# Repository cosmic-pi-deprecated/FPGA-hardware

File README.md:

# FPGA-hardware
FPGA main board for Cosmic Pi

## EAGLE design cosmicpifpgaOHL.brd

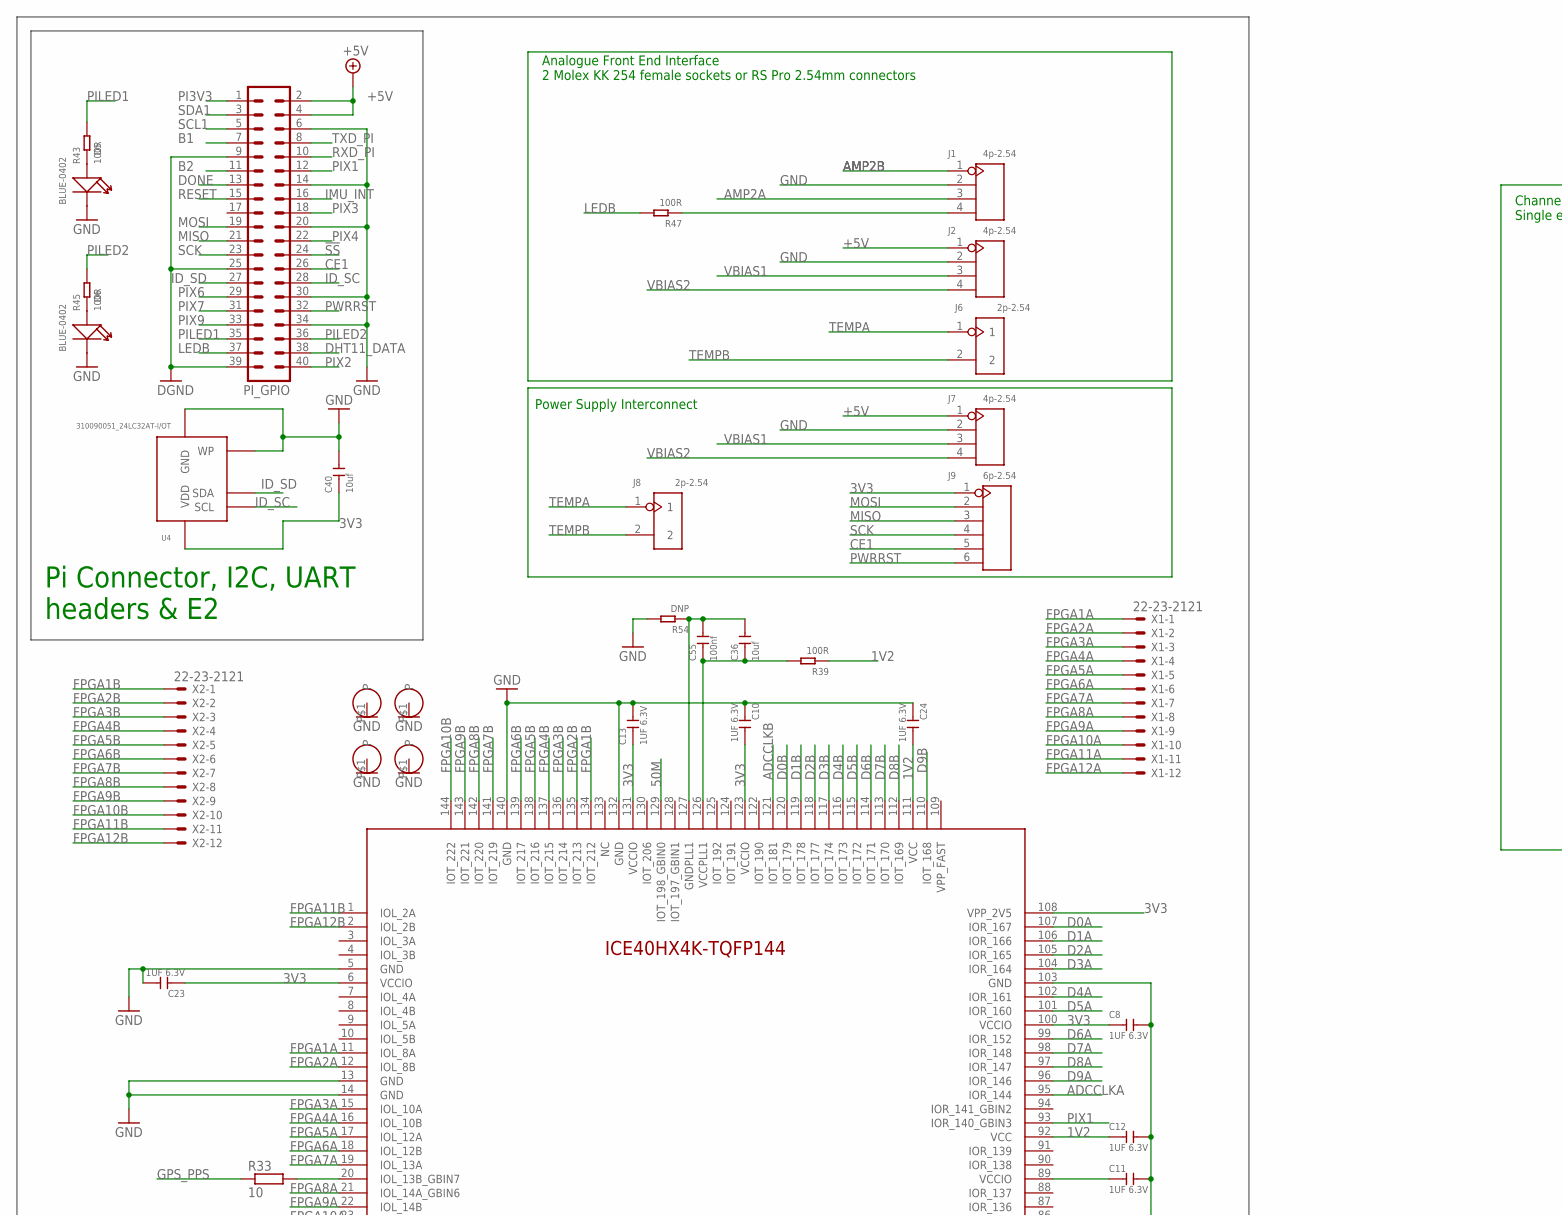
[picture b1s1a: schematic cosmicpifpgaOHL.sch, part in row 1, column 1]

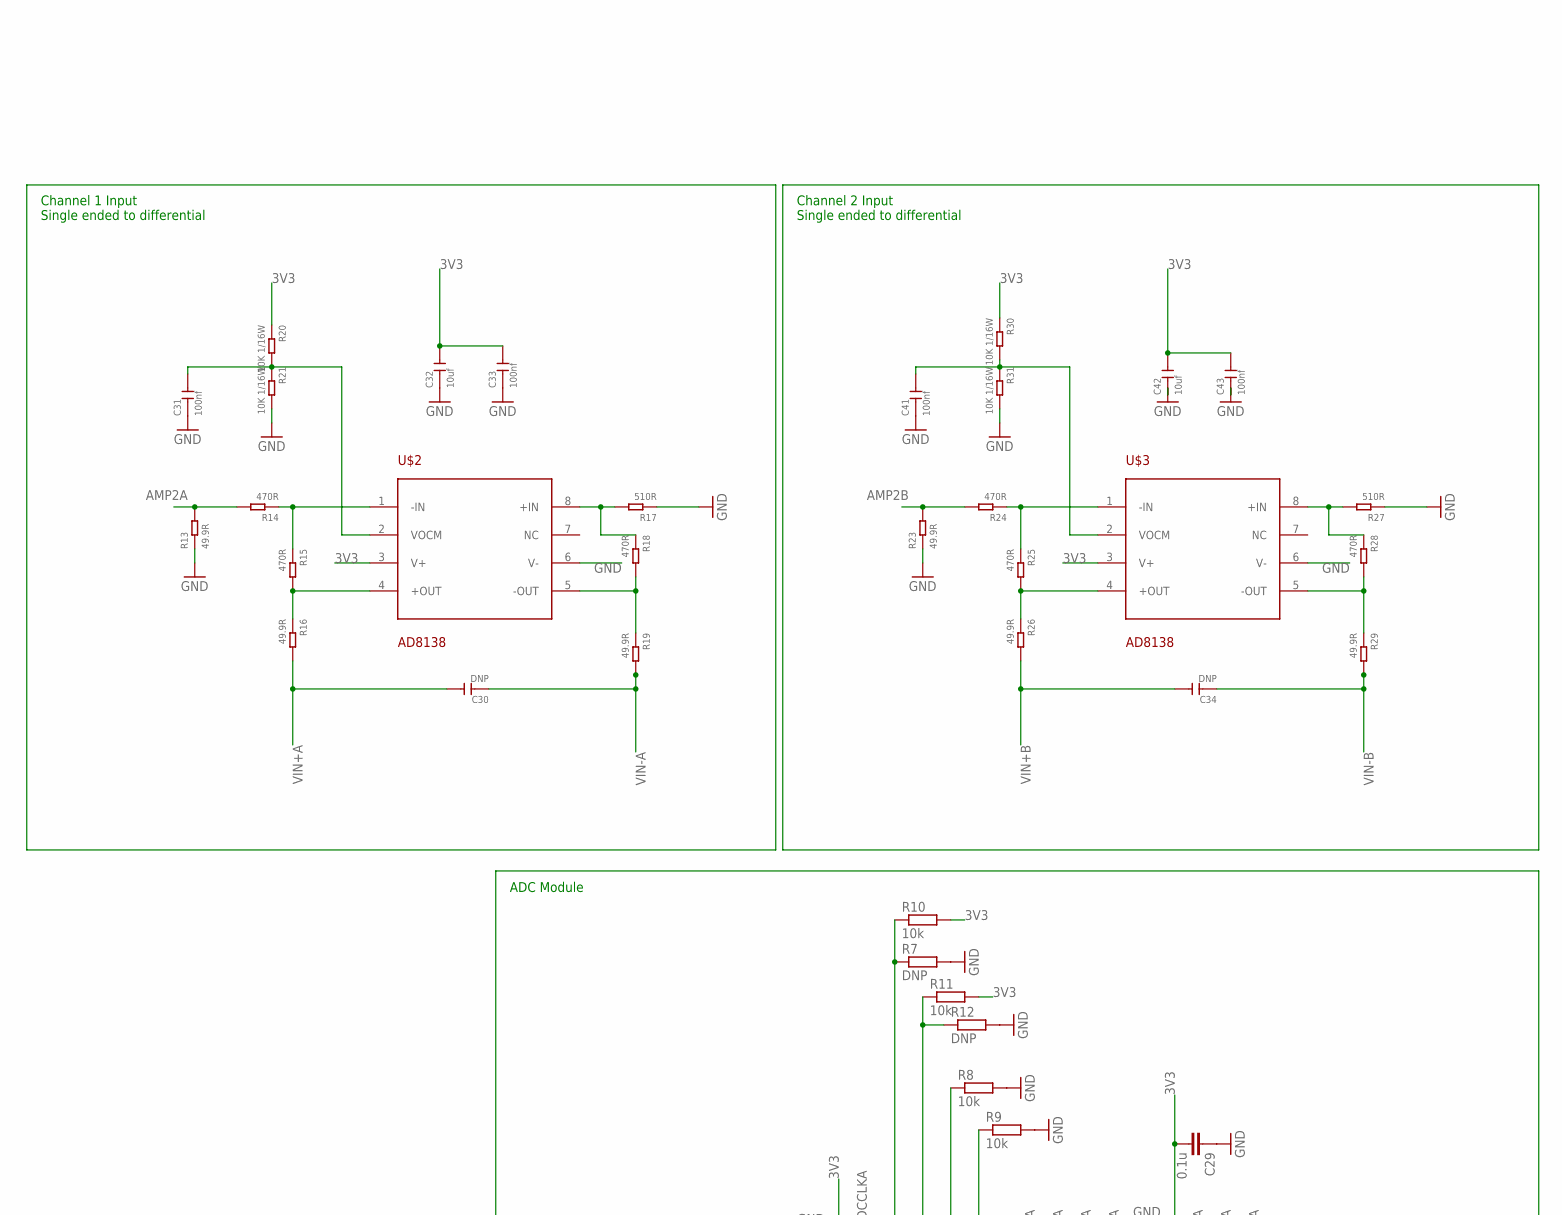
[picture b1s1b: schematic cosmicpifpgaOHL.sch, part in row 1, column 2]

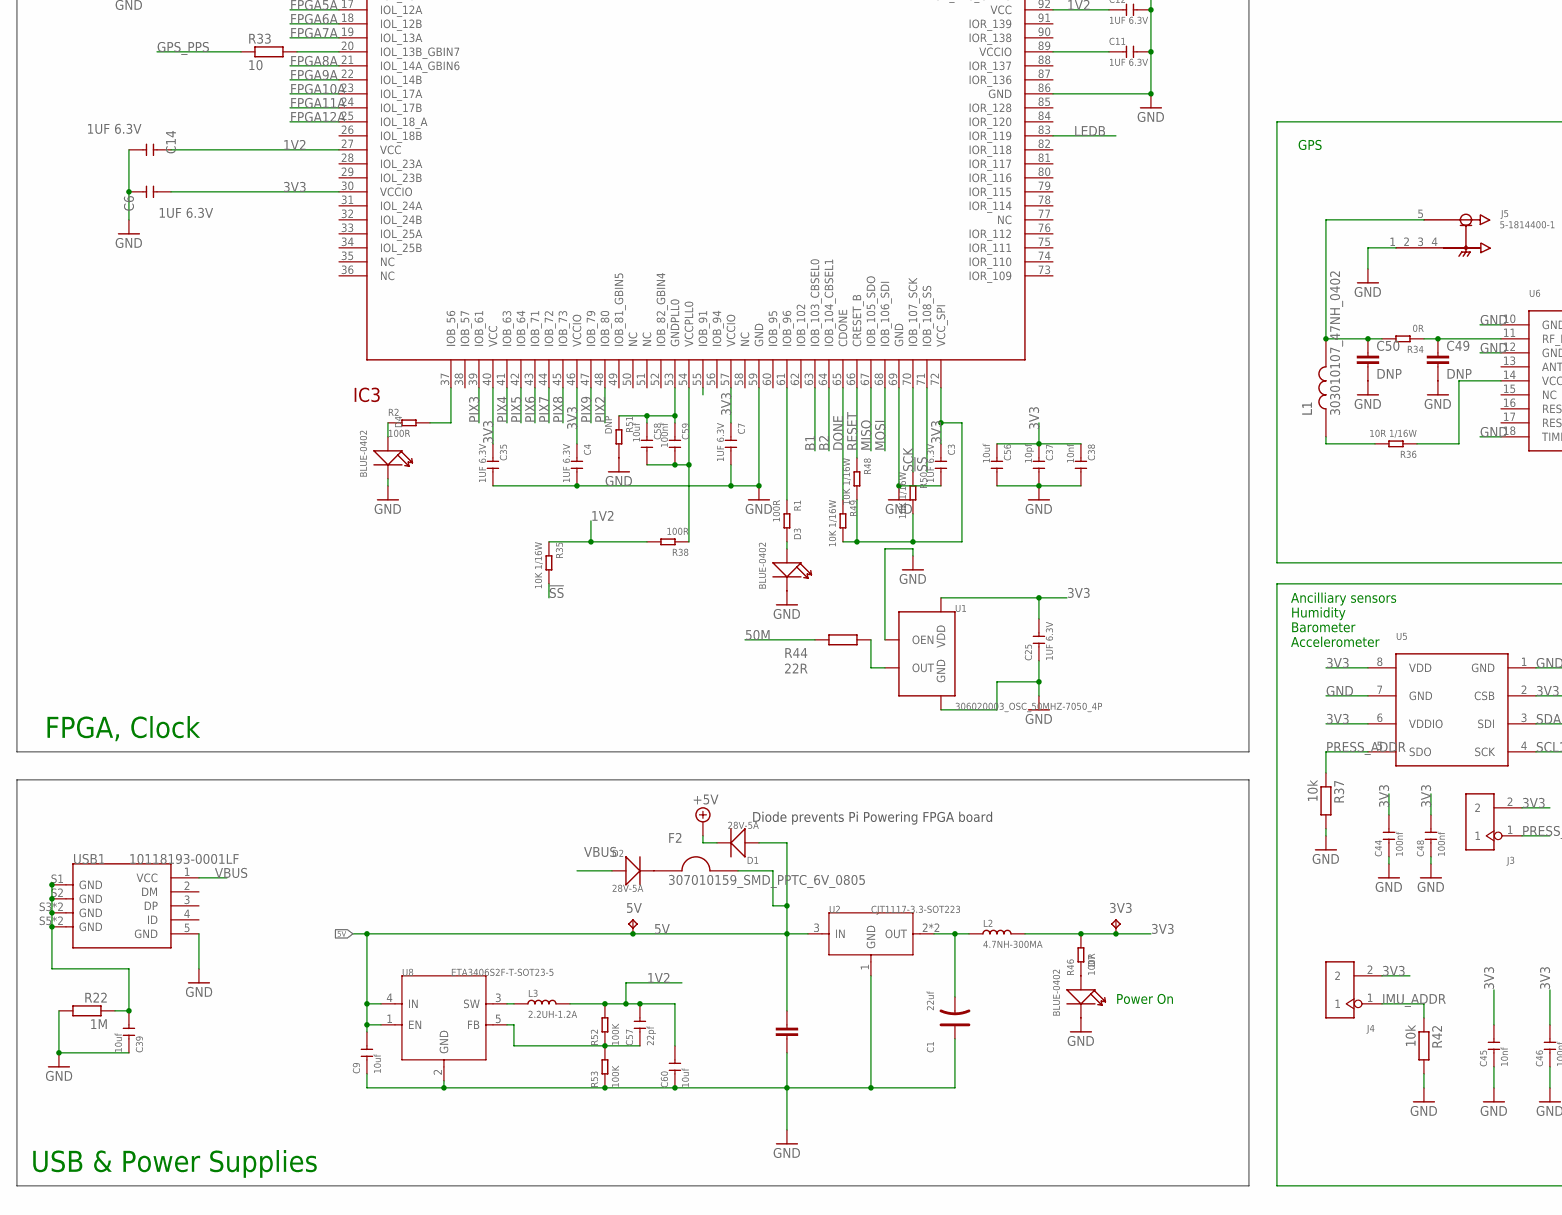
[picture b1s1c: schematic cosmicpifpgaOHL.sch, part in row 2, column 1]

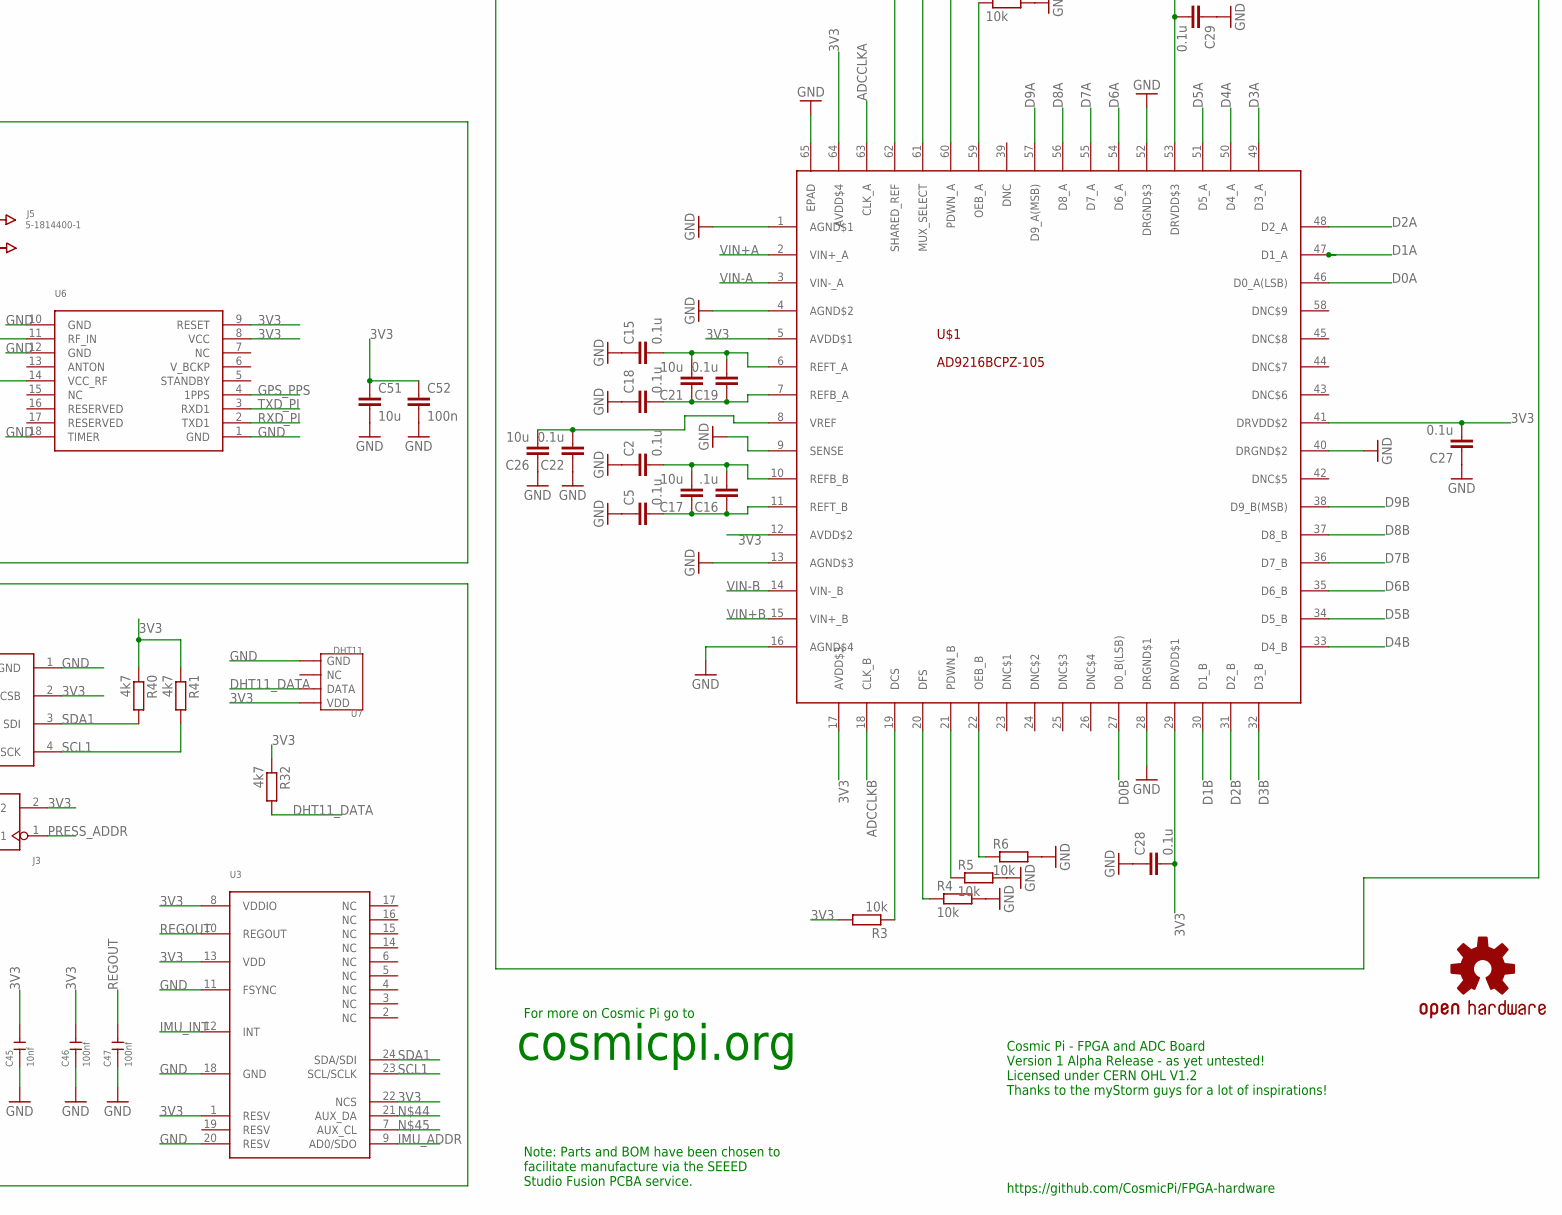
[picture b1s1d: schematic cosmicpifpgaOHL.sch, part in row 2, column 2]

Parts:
3V3, 5V: TPB1,27; B1,27
C1: 22uf; AVX-B
C2, C5, C15, C18, C19, C22, C27, C28, C29: 0.1u; C0402
C3, C4, C6, C7, C8, C10, C11, C12, C13, C14, C23, C24, C25, C35: 1UF 6.3V; C0402
C9, C32, C36, C39, C40, C42, C56, C58, C60: 10uf; C0402
C16: .1u; C0402
C17, C21, C26, C51: 10u; C0402
C20: 47uF; 1206
C30, C34: DNP; C0603
C31, C33, C41, C43, C44, C46, C47, C48, C55, C59: 100nf; C0402
C37: 10pf; C0402
C38, C45: 10nf; C0402
C49, C50: DNP; C0402
C52: 100n; C0402
C57: 22pf; C0402
D1, D2: 28V-5A; DO-214AA
D3, D4, D5, D6, D7: BLUE-0402; LED-0402
F2: 307010159_SMD_PPTC_6V_0805; F0805
IC3: ICE40HX4K_TQFP144; TQFP144
J1, J2, J7: 4p-2.54; H4-2.54
J3, J4: DIP-BLACK-JUMPER; H2-2.54
J5: 5-1814400-1; TE_5-1814400-1
J6, J8: 2p-2.54; H2-2.54
J9: 6p-2.54; H6-2.54
L1: 303010107_47NH_0402; L0402
L2: 4.7NH-300MA; L0402
L3: 2.2UH-1.2A; L0805
OSHW: OSHW-LOGOL; OSHW-LOGO-L
PI_GPIO: MA20-2
R1, R2, R38, R39, R43, R45, R46, R47: 100R; R0402
R3, R4, R5, R6, R8, R9, R10, R11, R37, R42: 10k; R0402
R7, R12, R51, R54: DNP; R0402
R13, R16, R19, R23, R26, R29: 49.9R; R0603
R14, R15, R18, R24, R25, R28: 470R; R0603
R17, R27: 510R; R0603
R20, R21, R30, R31, R35, R48, R49, R50: 10K 1/16W; R0402
R22: 1M; R0402
R32, R40, R41: 4k7; R0402
R33: 10; R0402
R34: 0R; R0402
R36: 10R 1/16W; R0402
R44: 22R; R0402
R52, R53: 100K; R0402
U1: 306020003_OSC_50MHZ-7050_4P; X7050_4P
U2: CJT1117-3.3-SOT223; SOT-223
U3: MPU-9250
U4: 310090051_24LC32AT-I/OT; SOT235
U5: BMP280
U6: L70-M39
U7: DHT11; SNR4-2.54-15.5X12.0X5.5MM
U8: ETA3406S2F-T-SOT23-5; SOT-23-5
U$1: AD9216BCPZ-105; QFN50P900X900X100-65N
U$2, U$3: AD8138; SOP65P490X110-8N
U$16, U$21, U$22, U$24: HOLE-2.5MM; 2.5MM-HOLE
USB1: 10118193-0001LF; MICRO-USB5+6P-SMD-0.65-B
X1, X2: 22-23-2121

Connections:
1V2: C12.1, C14.1, C24.2, C57.2, C60.2, IC3.27 (VCC), IC3.92 (VCC), IC3.111 (VCC), L3.2, R35.1, R38.2, R39.1, R52.2
3V3: 3V3.TP, C3.1, C4.1, C6.2, C7.1, C8.1, C10.2, C13.1, C23.1, C25.2, C27.2, C28.2, C29.2, C32.2, C33.2, C35.1, C37.1, C38.1, C40.1, C42.2, C43.2, C44.2, C45.2, C46.2, C48.2, C51.1, C52.1, C56.1, IC3.6 (VCCIO), IC3.30 (VCCIO), IC3.40 (VCC), IC3.46 (VCCIO), IC3.57 (VCCIO), IC3.72 (VCC_SPI), IC3.100 (VCCIO), IC3.108 (VPP_2V5), IC3.123 (VCCIO), IC3.131 (VCCIO), J3.2, J4.2, J9.1, L2.2, R3.2, R10.2, R11.2, R20.1, R30.1, R32.1, R40.1, R41.1, R46.2, R48.2, R49.2, R50.2, U1.P$4 (VDD), U3.1 (RESV), U3.8 (VDDIO), U3.13 (VDD), U3.22 (NCS), U4.4 (VDD), U5.2 (CSB), U5.6 (VDDIO), U5.8 (VDD), U6.8 (VCC), U6.9 (RESET), U7.1 (VDD), U$1.5 (AVDD$1), U$1.12 (AVDD$2), U$1.17 (AVDD$3), U$1.29 (DRVDD$1), U$1.41 (DRVDD$2), U$1.53 (DRVDD$3), U$1.64 (AVDD$4), U$2.3 (V+), U$3.3 (V+)
5V: 5V.TP, C9.2, C20.1, D1.+, F2.P$2, U2.3 (IN), U8.1 (EN), U8.4 (IN)
50M: IC3.129 (IOT_198_GBIN0), R44.2
!SS: IC3.71 (IOB_108_SS), PI_GPIO.24, R35.2
+5V: D1.-, J2.1, J7.1, PI_GPIO.2, PI_GPIO.4
ADCCLKA: IC3.95 (IOR_144), U$1.63 (CLK_A)
ADCCLKB: IC3.121 (IOT_181), U$1.18 (CLK_B)
AMP2A: J1.3, R13.2, R14.2
AMP2B: J1.1, R23.2, R24.2
B1: IC3.63 (IOB_103_CBSEL0), PI_GPIO.7
B2: IC3.64 (IOB_104_CBSEL1), PI_GPIO.11
CE1: J9.5, PI_GPIO.26
D0A: IC3.107 (IOR_167), U$1.46 (D0_A(LSB))
D0B: IC3.120 (IOT_179), U$1.27 (D0_B(LSB))
D1A: IC3.106 (IOR_166), U$1.47 (D1_A)
D1B: IC3.119 (IOT_178), U$1.30 (D1_B)
D2A: IC3.105 (IOR_165), U$1.48 (D2_A)
D2B: IC3.118 (IOT_177), U$1.31 (D2_B)
D3A: IC3.104 (IOR_164), U$1.49 (D3_A)
D3B: IC3.117 (IOT_174), U$1.32 (D3_B)
D4A: IC3.102 (IOR_161), U$1.50 (D4_A)
D4B: IC3.116 (IOT_173), U$1.33 (D4_B)
D5A: IC3.101 (IOR_160), U$1.51 (D5_A)
D5B: IC3.115 (IOT_172), U$1.34 (D5_B)
D6A: IC3.99 (IOR_152), U$1.54 (D6_A)
D6B: IC3.114 (IOT_171), U$1.35 (D6_B)
D7A: IC3.98 (IOR_148), U$1.55 (D7_A)
D7B: IC3.113 (IOT_170), U$1.36 (D7_B)
D8A: IC3.97 (IOR_147), U$1.56 (D8_A)
D8B: IC3.112 (IOT_169), U$1.37 (D8_B)
D9A: IC3.96 (IOR_146), U$1.57 (D9_A(MSB))
D9B: IC3.110 (IOT_168), U$1.38 (D9_B(MSB))
DHT11_DATA: PI_GPIO.38, R32.2, U7.2 (DATA)
DONE: IC3.65 (CDONE), PI_GPIO.13, R49.1
FPGA1A: IC3.11 (IOL_8A), X1.1
FPGA1B: IC3.134 (IOT_212), X2.1
FPGA2A: IC3.12 (IOL_8B), X1.2
FPGA2B: IC3.135 (IOT_213), X2.2
FPGA3A: IC3.15 (IOL_10A), X1.3
FPGA3B: IC3.136 (IOT_214), X2.3
FPGA4A: IC3.16 (IOL_10B), X1.4
FPGA4B: IC3.137 (IOT_215), X2.4
FPGA5A: IC3.17 (IOL_12A), X1.5
FPGA5B: IC3.138 (IOT_216), X2.5
FPGA6A: IC3.18 (IOL_12B), X1.6
FPGA6B: IC3.139 (IOT_217), X2.6
FPGA7A: IC3.19 (IOL_13A), X1.7
FPGA7B: IC3.141 (IOT_219), X2.7
FPGA8A: IC3.21 (IOL_14A_GBIN6), X1.8
FPGA8B: IC3.142 (IOT_220), X2.8
FPGA9A: IC3.22 (IOL_14B), X1.9
FPGA9B: IC3.143 (IOT_221), X2.9
FPGA10A: IC3.23 (IOL_17A), X1.10
FPGA10B: IC3.144 (IOT_222), X2.10
FPGA11A: IC3.24 (IOL_17B), X1.11
FPGA11B: IC3.1 (IOL_2A), X2.11
FPGA12A: IC3.25 (IOL_18_A), X1.12
FPGA12B: IC3.2 (IOL_2B), X2.12
GND: C1.+, C2.1, C3.2, C4.2, C5.1, C6.1, C7.2, C8.2, C9.1, C10.1, C11.2, C12.2, C13.2, C14.2, C15.1, C18.1, C20.2, C22.1, C23.2, C24.1, C25.1, C26.1, C27.1, C28.1, C29.1, C31.1, C32.1, C33.1, C35.2, C37.2, C38.2, C39.1, C40.2, C41.1, C42.1, C43.1, C44.1, C45.1, C46.1, C47.1, C48.1, C49.2, C50.2, C51.2, C52.2, C56.2, C60.1, D3.-, D4.-, D5.-, D6.-, D7.-, IC3.5 (GND), IC3.13 (GND), IC3.14 (GND), IC3.59 (GND), IC3.69 (GND), IC3.86 (GND), IC3.103 (GND), IC3.132 (GND), IC3.140 (GND), J1.2, J2.2, J5.1 (GND), J7.2, PI_GPIO.6, PI_GPIO.9, PI_GPIO.14, PI_GPIO.20, PI_GPIO.25, PI_GPIO.30, PI_GPIO.34, PI_GPIO.39, R4.2, R5.2, R6.2, R7.2, R8.2, R9.2, R12.2, R13.1, R17.1, R21.2, R22.2, R23.1, R27.1, R31.2, R37.2, R42.2, R51.2, R53.1, R54.2, U1.P$1 (OEN), U1.P$2 (GND), U2.1 (GND), U3.11 (FSYNC), U3.18 (GND), U3.20 (RESV), U4.2 (GND), U4.5 (WP), U5.1 (GND), U5.7 (GND), U6.1 (GND), U6.10 (GND), U6.12 (GND), U6.18 (TIMER), U7.4 (GND), U8.2 (GND), U$1.1 (AGND$1), U$1.4 (AGND$2), U$1.9 (SENSE), U$1.13 (AGND$3), U$1.16 (AGND$4), U$1.28 (DRGND$1), U$1.40 (DRGND$2), U$1.52 (DRGND$3), U$1.65 (EPAD), U$2.6 (V-), U$3.6 (V-), U$16.P$1, U$21.P$1, U$22.P$1, U$24.P$1, USB1.5 (GND)
GPS_PPS: R33.1, U6.4 (1PPS)
ID_SC: PI_GPIO.28, U4.1 (SCL)
ID_SD: PI_GPIO.27, U4.3 (SDA)
IMU_ADDR: J4.1, R42.1, U3.9 (AD0/SDO)
IMU_INT: PI_GPIO.16, U3.12 (INT)
LEDB: IC3.83 (IOR_119), PI_GPIO.37, R47.2
MISO: IC3.67 (IOB_105_SDO), J9.3, PI_GPIO.21
MOSI: IC3.68 (IOB_106_SDI), J9.2, PI_GPIO.19
unnamed: C2.2, C16.2, C17.2, U$1.10 (REFB_B)
unnamed: C36.1, C55.1, IC3.126 (VCCPLL1), R39.2
unnamed: C39.2, R22.1, USB1.S1 (GND), USB1.S2 (GND), USB1.S3 (GND), USB1.S4 (GND), USB1.S5 (GND), USB1.S6 (GND)
unnamed: D3.+, R1.2
unnamed: C5.2, C16.1, C17.1, U$1.11 (REFT_B)
unnamed: C15.2, C19.2, C21.2, U$1.6 (REFT_A)
unnamed: R44.1, U1.P$3 (OUT)
unnamed: D2.-, F2.P$1
unnamed: C18.2, C19.1, C21.1, U$1.7 (REFB_A)
unnamed: R6.1, U$1.22 (OEB_B)
unnamed: IC3.37 (IOB_56), R2.2
unnamed: D4.+, R2.1
unnamed: C22.2, C26.2, U$1.8 (VREF)
unnamed: R5.1, U$1.21 (PDWN_B)
unnamed: R4.1, U$1.20 (DFS)
unnamed: R3.1, U$1.19 (DCS)
unnamed: C58.2, C59.2, IC3.54 (VCCPLL0), R38.1
unnamed: IC3.20 (IOL_13B_GBIN7), R33.2
unnamed: IC3.61 (IOB_96), R1.1
unnamed: R7.1, R10.1, U$1.62 (SHARED_REF)
unnamed: R11.1, R12.1, U$1.61 (MUX_SELECT)
unnamed: R8.1, U$1.60 (PDWN_A)
unnamed: R9.1, U$1.59 (OEB_A)
unnamed: R14.1, R15.1, U$2.1 (-IN)
unnamed: C1.-, L2.1, U2.2 (OUT), U2.TER (OUT)
unnamed: R15.2, R16.1, U$2.4 (+OUT)
unnamed: C11.1, IC3.89 (VCCIO)
unnamed: C31.2, R20.2, R21.1, U$2.2 (VOCM)
unnamed: R17.2, R18.1, U$2.8 (+IN)
unnamed: R18.2, R19.1, U$2.5 (-OUT)
unnamed: R24.1, R25.1, U$3.1 (-IN)
unnamed: R25.2, R26.1, U$3.4 (+OUT)
unnamed: C41.2, R30.2, R31.1, U$3.2 (VOCM)
unnamed: R27.2, R28.1, U$3.8 (+IN)
unnamed: R28.2, R29.1, U$3.5 (-OUT)
unnamed: D5.+, R43.1
unnamed: D6.+, R45.1
unnamed: D7.+, R46.1
unnamed: J1.4, R47.1
unnamed: C58.1, C59.1, IC3.53 (GNDPLL0), R51.1
unnamed: C36.2, C55.2, IC3.127 (GNDPLL1), R54.1
unnamed: L3.1, U8.3 (SW)
unnamed: C57.1, R52.1, R53.2, U8.5 (FB)
PI3V3: PI_GPIO.1
PILED1: PI_GPIO.35, R43.2
PILED2: PI_GPIO.36, R45.2
PIX1: IC3.93 (IOR_140_GBIN3), PI_GPIO.12
PIX2: IC3.48 (IOB_80), PI_GPIO.40
PIX3: IC3.39 (IOB_61), PI_GPIO.18
PIX4: IC3.41 (IOB_63), PI_GPIO.22
PIX5: IC3.42 (IOB_64)
PIX6: IC3.43 (IOB_71), PI_GPIO.29
PIX7: IC3.44 (IOB_72), PI_GPIO.31
PIX8: IC3.45 (IOB_73)
PIX9: IC3.47 (IOB_79), PI_GPIO.33
PIX13: IC3.55 (IOB_91)
PRESS_ADDR: J3.1, R37.1, U5.5 (SDO)
PWRRST: J9.6, PI_GPIO.32
REGOUT: C47.2, U3.10 (REGOUT)
RESET: IC3.66 (CRESET_B), PI_GPIO.15, R48.1
RF_IN: C49.1, R34.1, U6.11 (RF_IN)
RF_IN2: C50.1, J5.5 (SIG), L1.P$2, R34.2
RXD_PI: PI_GPIO.10, U6.2 (TXD1)
SCK: IC3.70 (IOB_107_SCK), J9.4, PI_GPIO.23, R50.1
SCL1: PI_GPIO.5, R41.2, U3.23 (SCL/SCLK), U5.4 (SCK)
SDA1: PI_GPIO.3, R40.2, U3.24 (SDA/SDI), U5.3 (SDI)
TEMPA: J6.1, J8.1
TEMPB: J6.2, J8.2
TXD_PI: PI_GPIO.8, U6.3 (RXD1)
VBIAS1: J2.3, J7.3
VBIAS2: J2.4, J7.4
VBUS: D2.+, USB1.1 (VCC)
VCC_RF: R36.1, U6.14 (VCC_RF)
VCC_RF2: L1.P$1, R36.2
VIN+A: C30.2, R16.2, U$1.2 (VIN+_A)
VIN+B: C34.2, R26.2, U$1.15 (VIN+_B)
VIN-A: C30.1, R19.2, U$1.3 (VIN-_A)
VIN-B: C34.1, R29.2, U$1.14 (VIN-_B)

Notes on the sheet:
Diode prevents Pi Powering FPGA board
Pi Connector, I2C, UART headers & E2
FPGA, Clock
USB & Power Supplies
GPS
ADC Module
Channel 1 Input Single ended to differential
Channel 2 Input Single ended to differential
Ancilliary sensors Humidity Barometer Accelerometer
Analogue Front End Interface 2 Molex KK 254 female sockets or RS Pro 2.54mm connectors
Power Supply Interconnect
Power On
Cosmic Pi - FPGA and ADC Board Version 1 Alpha Release - as yet untested! Licensed under CERN OHL V1.2 Thanks to the myStorm guys for a lot of inspirations!
https://github.com/CosmicPi/FPGA-hardware
Note: Parts and BOM have been chosen to facilitate manufacture via the SEEED Studio Fusion PCBA service.
For more on Cosmic Pi go to
cosmicpi.org

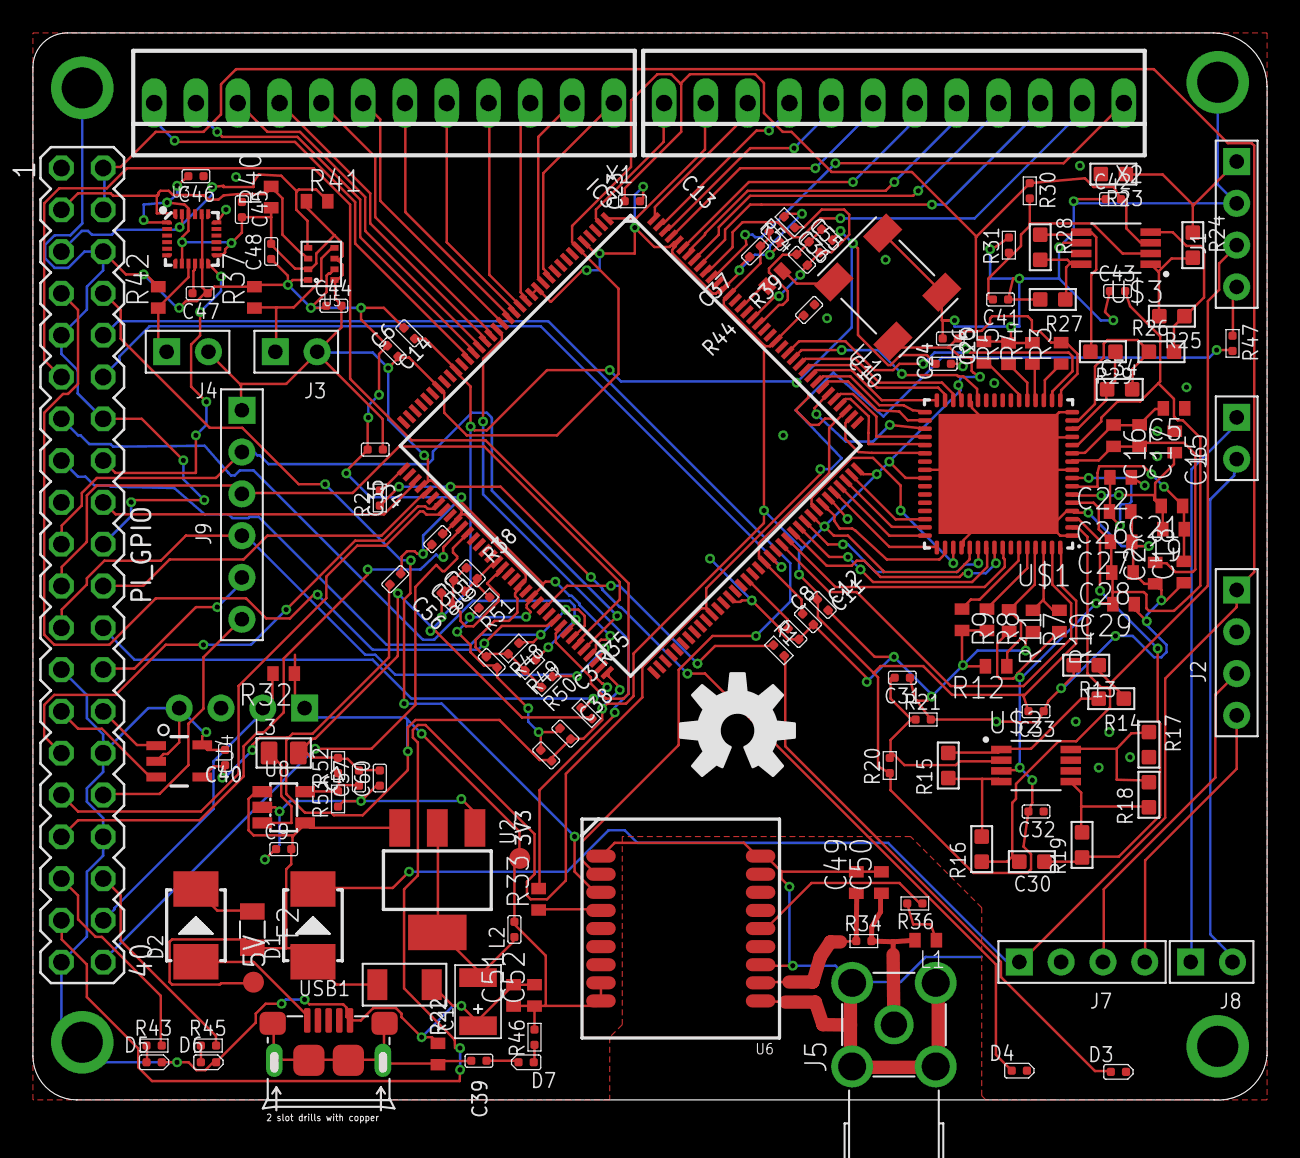
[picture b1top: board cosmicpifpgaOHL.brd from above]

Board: 2 copper layers, 75.0 x 65.5 mm, 155 parts (1 on the bottom side), 142 nets.

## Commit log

2017-09-08 First release
    Currently being manufactured by SEEED studio, note that for our first production run of prototypes we haven't included the ADC components to save some money.
2017-10-02 Fixed mirroring in schematic

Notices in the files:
parts and their libraries:
SparkFun-Aesthetics: Licensing: Creative Commons ShareAlike 4.0 International - https://creativecommons.org/licenses/by-sa/4.0
